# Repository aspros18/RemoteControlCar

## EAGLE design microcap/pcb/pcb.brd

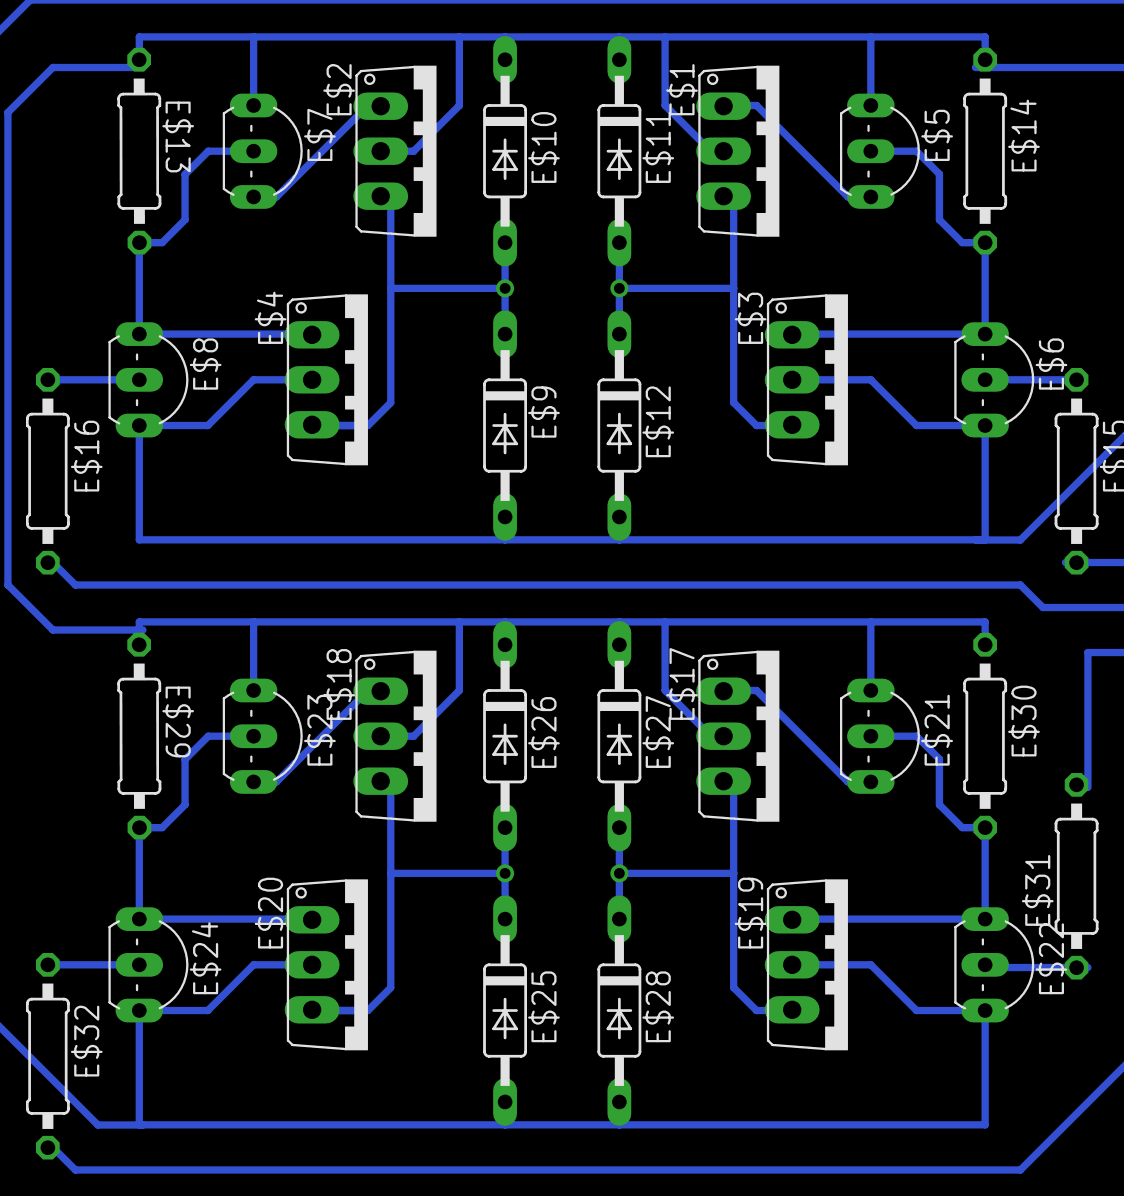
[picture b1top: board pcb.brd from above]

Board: 2 copper layers, 32 parts (0 on the bottom side), 15 nets.

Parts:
E$1, E$2, E$3, E$4, E$17, E$18, E$19, E$20: T-30_V
E$5, E$6, E$7, E$8, E$21, E$22, E$23, E$24: TO92-BCE
E$9, E$10, E$11, E$12, E$25, E$26, E$27, E$28: C2992
E$13, E$14, E$15, E$16, E$29, E$30, E$31, E$32: 0207/10

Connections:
S$1: E$8.C, E$16.1
S$2: E$7.C, E$8.B
S$4: E$23.C, E$24.B
S$7: E$5.B, E$7.B, E$10.C, E$11.C, E$14.1
S$9: E$9.C, E$10.A
S$10: E$11.A, E$12.C
S$12: E$6.C, E$15.1
S$13: E$6.E, E$8.E, E$9.A, E$12.A
S$14: E$5.C, E$6.B, E$14.2
S$33: E$24.C, E$32.1
S$50: E$25.C, E$26.A
S$55: E$27.A, E$28.C
S$56: E$21.B, E$23.B, E$26.C, E$27.C, E$30.1
S$59: E$22.E, E$24.E, E$25.A, E$28.A
S$60: E$21.C, E$22.B, E$30.2

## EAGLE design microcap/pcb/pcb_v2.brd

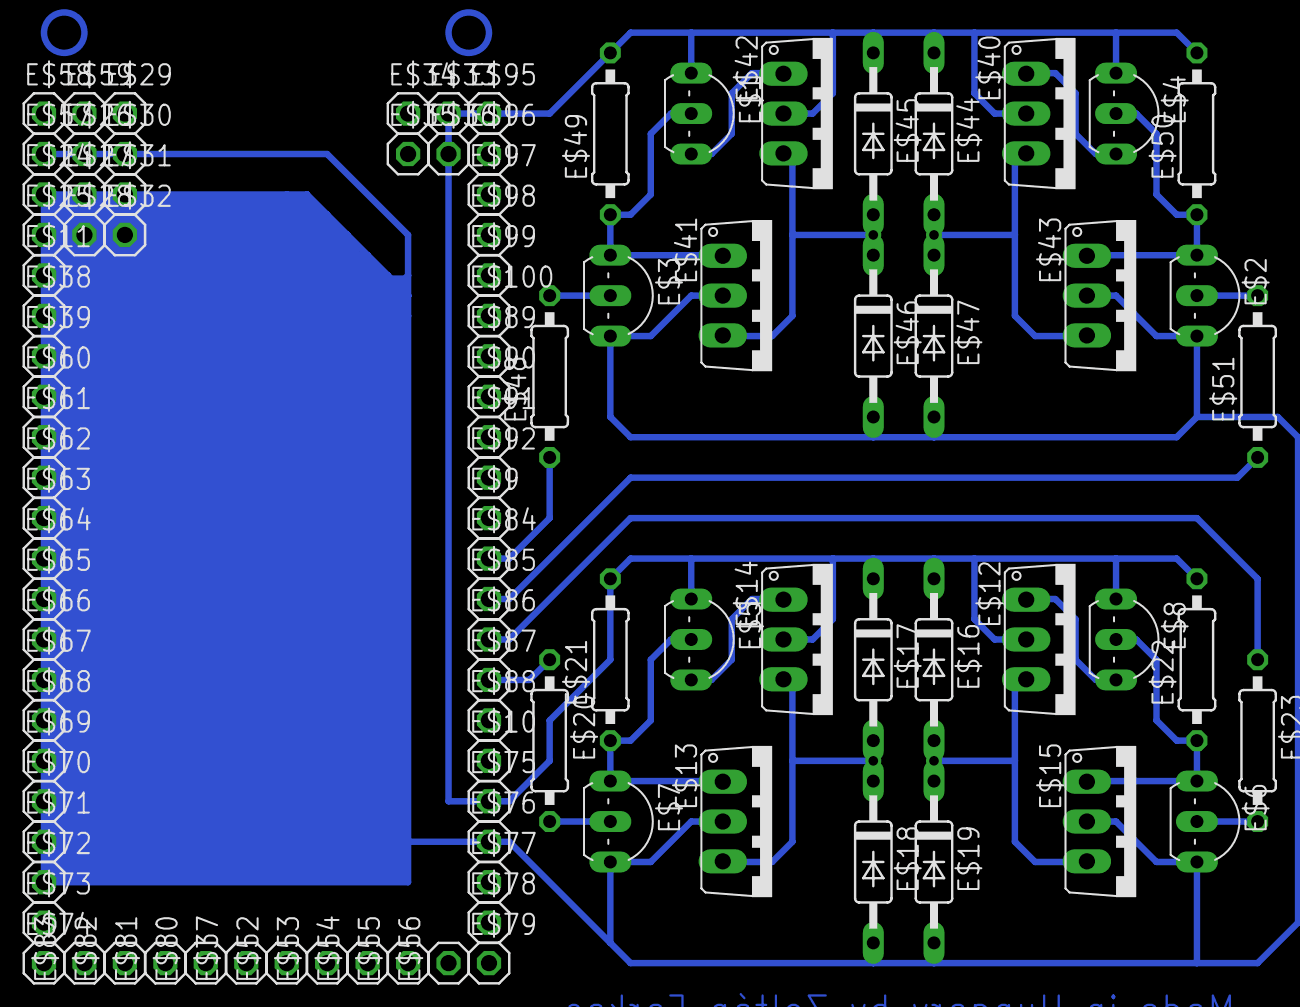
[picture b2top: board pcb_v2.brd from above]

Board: 2 copper layers, 98 parts (0 on the bottom side), 18 nets.

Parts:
E$1, E$2, E$3, E$4, E$5, E$6, E$7, E$8: TO92-CBE
E$9, E$10, E$11, E$24, E$25, E$26, E$27, E$28, E$29, E$30, E$31, E$32, E$33, E$34, E$35, E$36, E$37, E$38, E$39, E$52, E$53, E$54, E$55, E$56, E$57, E$58, E$59, E$60, E$61, E$62, E$63, E$64, E$65, E$66, E$67, E$68, E$69, E$70, E$71, E$72, E$73, E$74, E$75, E$76, E$77, E$78, E$79, E$80, E$81, E$82, E$83, E$84, E$85, E$86, E$87, E$88, E$89, E$90, E$91, E$92, E$95, E$96, E$97, E$98, E$99, E$100: 1X01
E$12, E$13, E$14, E$15, E$40, E$41, E$42, E$43: T-30_V
E$16, E$17, E$18, E$19, E$44, E$45, E$46, E$47: C2992
E$20, E$21, E$22, E$23, E$48, E$49, E$50, E$51: 0207/10

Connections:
S$2: E$2.C, E$4.B, E$50.1
S$5: E$3.B, E$48.2
S$6: E$2.B, E$51.2
S$7: E$5.B, E$7.C, E$21.1
S$8: E$2.E, E$3.E, E$6.E, E$7.E, E$18.A, E$19.A, E$24.1, E$26.1, E$46.A, E$47.A, E$57.1, E$72.1
S$9: E$1.B, E$3.C, E$49.1
S$12: E$17.A, E$18.C
S$15: E$1.C, E$4.C, E$5.C, E$8.C, E$16.C, E$17.C, E$21.2, E$22.2, E$33.1, E$44.C, E$45.C, E$49.2, E$50.2, E$75.1, E$95.1
S$16: E$6.C, E$8.B, E$22.1
S$17: E$6.B, E$23.2
S$18: E$20.1, E$87.1
S$19: E$16.A, E$19.C
S$20: E$51.1, E$85.1
S$21: E$7.B, E$20.2
S$22: E$45.A, E$46.C
S$23: E$48.1, E$84.1
S$24: E$23.1, E$86.1
S$25: E$44.A, E$47.C
